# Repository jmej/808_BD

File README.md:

# 808 kick drum from μ-rave 

[jmej](http://www.anestheticaudio.com/), [xnor](http://x37v.info)

## Notes

This is a near exact clone of the famous kick drum from the classic tr-808 drum
machine. The only changes are for facilitating the common mods (extended decay
and a pitch pot), and a slightly more flexible trigger input.

This can be triggered by a trigger output of a drum machine, or by a CV/Trigger
from a modular synth, a cmos square wave, or even a loud audio transient.
Alternatively you could wire a switch or button to send the trigger input high
as well. (Basically a quick +V to the trigger input does the job).

It runs on +/- power supply, you can run 2 9v batteries in series, or run it
off a bipolar (+/-15v or +/-12v power supply). Or... experiment!

The accent has a pull-up so if you'll have max volume if its not driven otherwise.

This is an easy and cheap build.

## Build Docs
[modwiggler build thread](http://www.modwiggler.com/forum/viewtopic.php?t=54149)

## BOM
XXX EDIT THIS FOR NEW VERSION
[Old Mouser BOM](http://www.mouser.com/ProjectManager/ProjectDetail.aspx?AccessID=950b04d9fc)

## Purchase
[tindie](https://www.tindie.com/products/jmej/808-kick-drum-clone-pcb/)

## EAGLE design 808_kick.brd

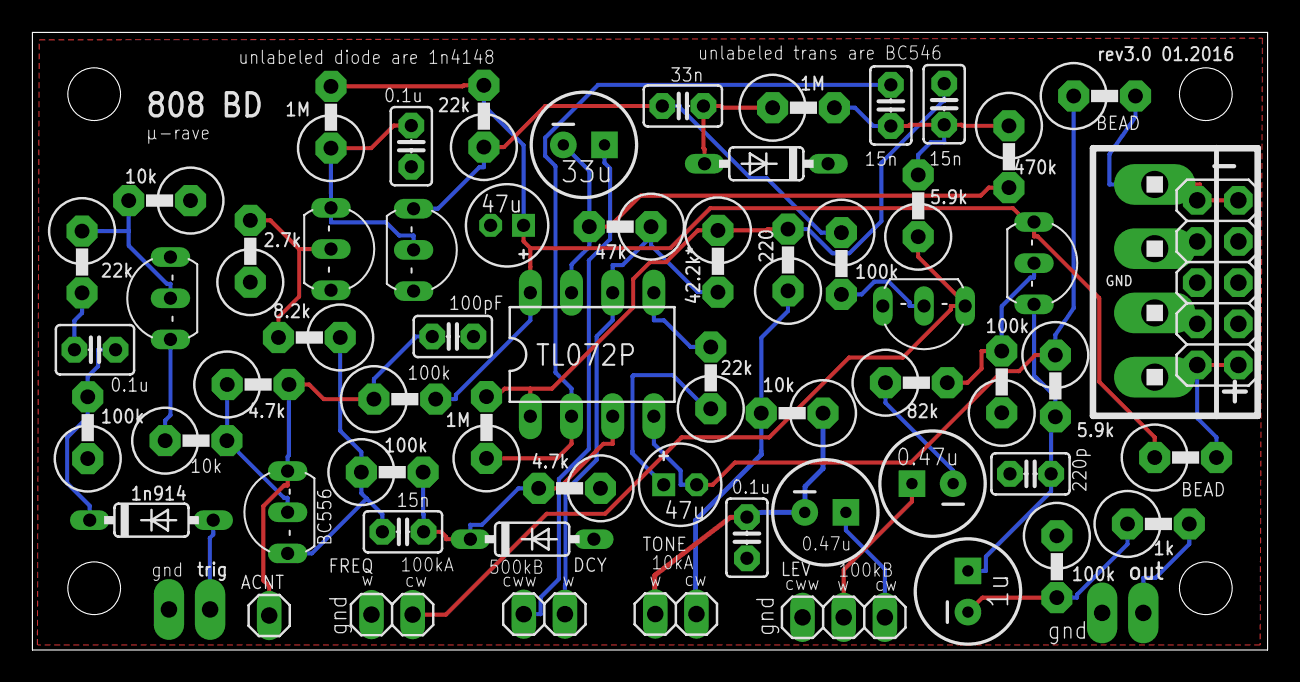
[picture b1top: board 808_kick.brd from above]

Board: 2 copper layers, 76.2 x 38.1 mm, 63 parts (0 on the bottom side), 36 nets.

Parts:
ACNT: 1X01
C1: 0.1u; C2.5-3
C2, C5: 0.47u; CPOL-RADIAL-100UF-25V
C3: 1u; CPOL-RADIAL-100UF-25V
C4, C7: 47u; E2-5
C6: 33u; CPOL-RADIAL-100UF-25V
C8, C10: 0.1u; C2.5-2
C9, C11, C14: 15n; C2.5-2
C12: 33n; C2.5-2
C13: 220p; C2.5-2
C15: 100pF; C2.5-2
D1, D2: 1N4148DO35-7; DO35-7
D3: IN914; DO35-7
DCY: 500kB; 1X02
EURO_POWER: 2X05
FREQ: 100kA; 1X02
IC2: TL072P; DIL08
LEV: 100kB; 1X03
MOTM_POWER: 1X4MTA
OUT: 1X02_LONGPADS
R1, R9, R25: 22k; 0411V
R2, R21, R27: 10k; 0411V
R3, R10, R14, R18, R19, R26: 100k; 0411V
R4, R23: 4.7k; 0411V
R5: 8.2k; 0411V
R6: 2.7k; 0411V
R7, R16, R22: 1M; 0411V
R8: 220; 0411V
R11: 47k; 0411V
R12: 1k; 0411V
R13, R17: 5.9k; 0411V
R15: 82k; 0411V
R20: 42.2k*; 0411V
R24: 470k; 0411V
R28, R29: BEAD; 0411V
T1, T2, T3, T5, T6: BC546A; TO92-EBC
T4: BC556; TO92-EBC
TONE: 10kA; 1X02
TRIG: 1X02_LONGPADS

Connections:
+15V: C7.+, IC2.8, R7.2, R9.2, R18.2, R29.1, T6.C
-15V: C4.-, IC2.4, R13.1, R28.1
GND: C4.+, C7.-, C8.2, C10.2, C13.2, C15.2, D1.C, D2.A, EURO_POWER.3, EURO_POWER.4, EURO_POWER.5, EURO_POWER.6, EURO_POWER.7, EURO_POWER.8, FREQ.1, LEV.1, MOTM_POWER.2, MOTM_POWER.3, OUT.2, R2.1, R6.1, R10.1, R14.1, R23.1, R25.1, R26.1, T1.E, T2.E, T3.E, T5.E, TRIG.2
unnamed: D3.A, TRIG.1
unnamed: R1.1, R2.2, T5.B
unnamed: R4.1, R27.2, T4.B
unnamed: ACNT.1, C15.1, R4.2, R18.1, T4.E
unnamed: C14.1, R3.1, R5.1, T4.C
unnamed: C14.2, D2.C, IC2.3, R3.2, R23.2
unnamed: FREQ.2, R17.1, T3.C
unnamed: C9.1, IC2.2, R16.1
unnamed: C6.1, DCY.2
unnamed: R5.2, R6.2, T2.B
unnamed: C8.1, R7.1, T1.B, T2.C
unnamed: OUT.1, R12.2
unnamed: C12.1, R9.1, R19.1, T1.C
unnamed: C12.2, D1.A, R22.1
unnamed: C3.1, C13.1, R13.2, T6.E
unnamed: C9.2, C11.1, R17.2, R22.2, R24.1
unnamed: R14.2, R15.2, T6.B
unnamed: C1.1, D3.C, R26.2
unnamed: C5.2, R15.1
unnamed: C3.2, R10.2, R12.1
unnamed: R19.2, T3.B
unnamed: R27.1, T5.C
unnamed: C11.2, IC2.1, R8.2, R16.2, R20.1
unnamed: R8.1, R21.2, TONE.1
unnamed: IC2.5, R25.2
unnamed: C5.1, LEV.2
unnamed: C6.2, IC2.7, R11.2, R24.2
unnamed: C1.2, R1.2
unnamed: DCY.1, IC2.6, R11.1, R20.2
unnamed: C2.1, LEV.3
unnamed: C2.2, C10.1, R21.1, TONE.2
NEG_INPUT: EURO_POWER.1, EURO_POWER.2, MOTM_POWER.4, R28.2
POS_INPUT: EURO_POWER.9, EURO_POWER.10, MOTM_POWER.1, R29.2

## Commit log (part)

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2016-01-15 added pullup for accent input
    so it'll be normally high
2016-01-15 cleaned up the schematic a little bit
2016-01-15 added MOTM style power
2016-01-15 ignoring lock files
2016-01-16 added euro power
2016-01-16 board layout, increased size too
2016-01-16 cleaned up the project, took version out of project files
2016-01-16 readme sub headings
2016-01-16 updated link
2016-01-16 moved stuff around on the schematic just to be more clear
2016-01-16 ditched some labels
2016-01-16 updated ignores for freerouting stuff
2016-01-16 converted pot i/o into 2 pin when there were 2 ganged pins
    I'd gang the pot on the pot itself anyways
2016-01-16 minor edits
2016-01-17 routed!
2016-01-17 fixed up some layers for oshpark
2016-01-17 moved the bead a little further away from the screw hole
2016-01-17 moved the trig further away from screw hole
2016-01-17 swapped tone pins, labeled pot connections
